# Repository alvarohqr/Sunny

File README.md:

# A LoRaWAN Air Quality and Meteorological monitoring system based on a MSP430FR5529LP Texas Instruments launchpad.

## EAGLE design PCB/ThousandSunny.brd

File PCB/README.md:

Thousand Sunny Printed Circuit Board Files.
Software: EaglePCB for designd and EasyEDA for costumization.

IMPORTANT NOTE: the Protection Circuit uses a IRF9Z34 transistor while the Power Saving Circuit a IRLZ44N.

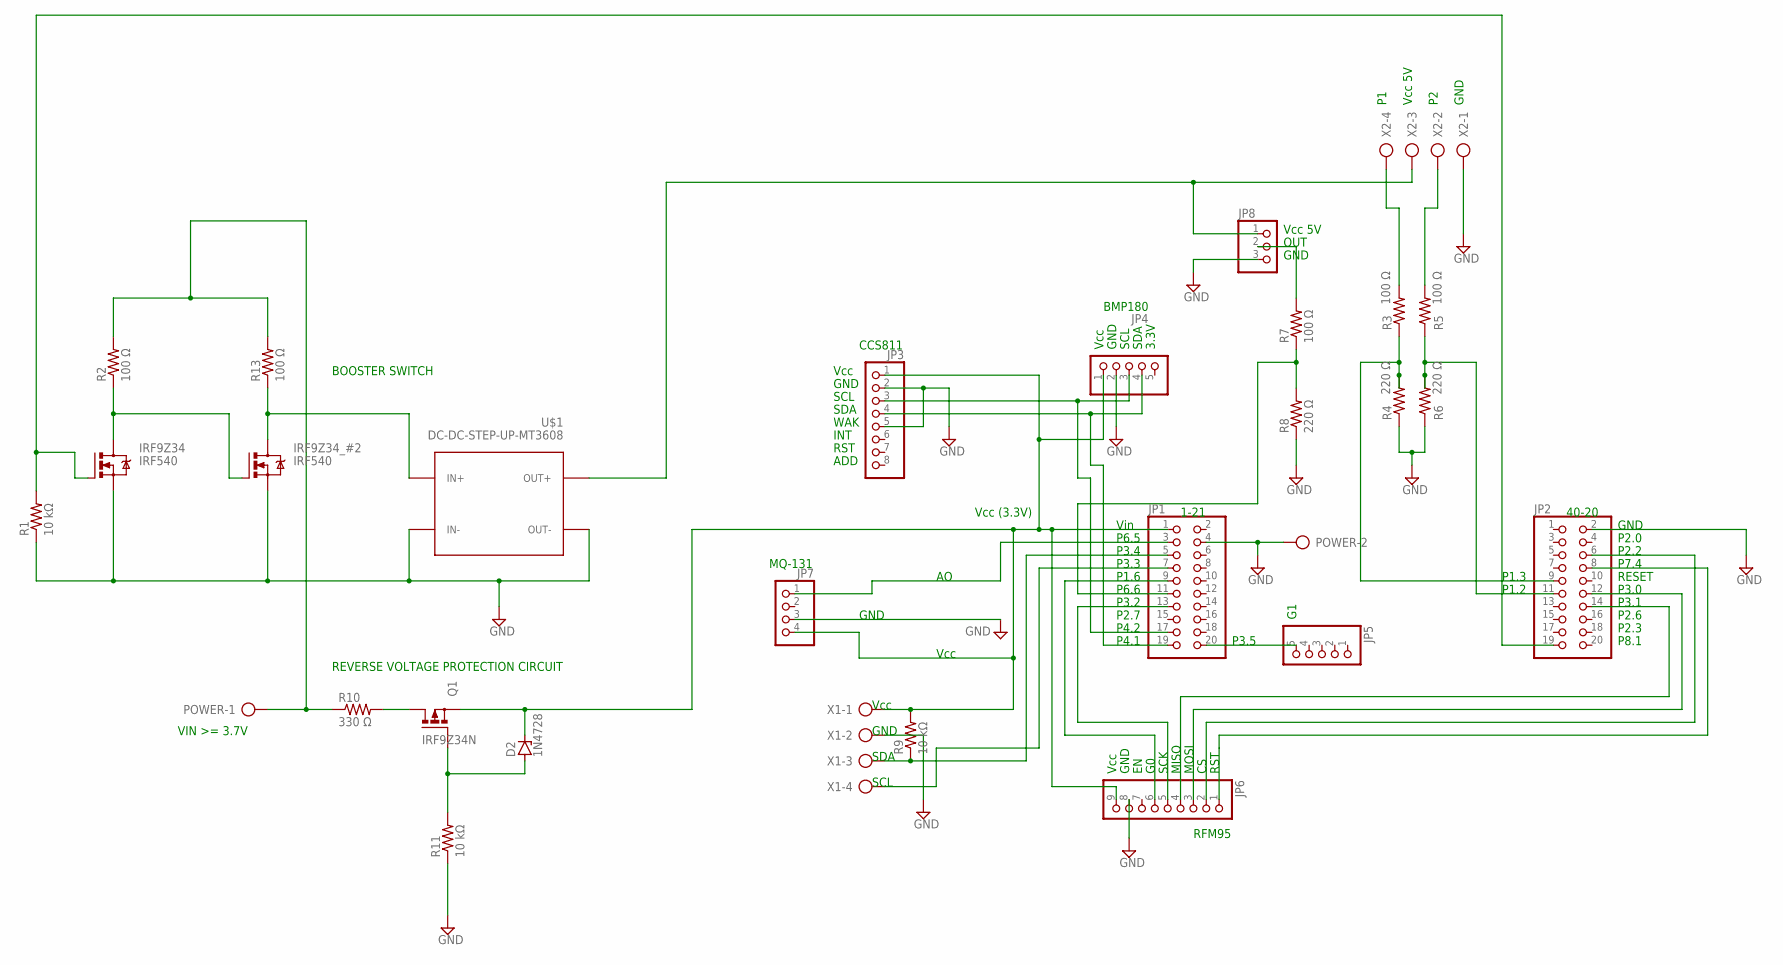
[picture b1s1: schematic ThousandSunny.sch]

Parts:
D2: 1N4728; DO41Z10
IRF9Z34, IRF9Z34_#2: IRF540; TO220BV
JP1, JP2: PINHD-2X10; 2X10
JP3: PINHD-1X8; 1X08
JP4, JP5: PINHD-1X5; 1X05
JP6: PINHD-1X9; 1X09
JP7: PINHD-1X4; 1X04
JP8: PINHD-1X3; 1X03
POWER: AK300/2
Q1: IRF9Z34N; TO220BV
R1, R9, R11: 10 kΩ; 0204/7
R2, R3, R5, R7, R13: 100 Ω; 0204/7
R4, R6, R8: 220 Ω; 0204/7
R10: 330 Ω; 0204/7
U$1: DC-DC-STEP-UP-MT3608
X1, X2: AK300/4

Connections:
ANODE: D2.A, Q1.G, R11.2
BATTERY: POWER.1, R2.2, R10.1, R13.2
D1->G2: IRF9Z34.D, IRF9Z34_#2.G, R2.1
D2->VIN: IRF9Z34_#2.D, R13.1, U$1.IN+
DRAIN_Q1: Q1.D, R10.2
DUST_P1: JP2.9, R3.1, R4.2
DUST_P2: JP2.11, R5.1, R6.2
G1: JP1.20, JP5.5
GND: IRF9Z34.S, IRF9Z34_#2.S, JP1.4, JP2.2, JP3.2, JP3.5, JP4.2, JP6.8, JP7.3, JP8.3, POWER.2, R1.1, R4.1, R6.1, R8.1, R11.1, U$1.IN-, U$1.OUT-, X1.2, X2.1
MISO: JP2.14, JP6.4
MOSI: JP2.12, JP6.3
O3: JP1.3, JP7.1
P8.2: IRF9Z34.G, JP2.19, R1.2
RAW_P1: R3.2, X2.4
RAW_P2: R5.2, X2.2
RAW_SOLAR: JP8.2, R7.2
RFM95W_CS: JP2.6, JP6.2
RFM95W_G0: JP1.9, JP6.6
RFM95_RST: JP2.8, JP6.1
SCK: JP1.13, JP6.5
SCL: JP1.17, JP3.3, JP4.3
SDA: JP1.19, JP3.4, JP4.4
SHT_CLOCK: JP1.7, X1.4
SHT_DATA: JP1.5, R9.1, X1.3
SOLAR: JP1.11, R7.1, R8.2
VIN->DUST: JP8.1, U$1.OUT+, X2.3
VZ->3.3V: D2.C, JP1.1, JP3.1, JP4.1, JP6.9, JP7.4, Q1.S, R9.2, X1.1

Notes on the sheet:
Vcc (3.3V)
Vcc
GND
SCK
MISO
MOSI
RST
Vin
P6.5
P3.4
P3.3
P1.6
P6.6
P3.2
P2.7
P4.2
P4.1
SCL
SDA
WAK
INT
ADD
P2.0
P7.4
RESET
P3.0
P3.1
P2.6
P2.3
P8.1
P2.2
P3.5
P1.3
P1.2
3.3V
Vcc 5V
1-21
40-20
CCS811
BMP180

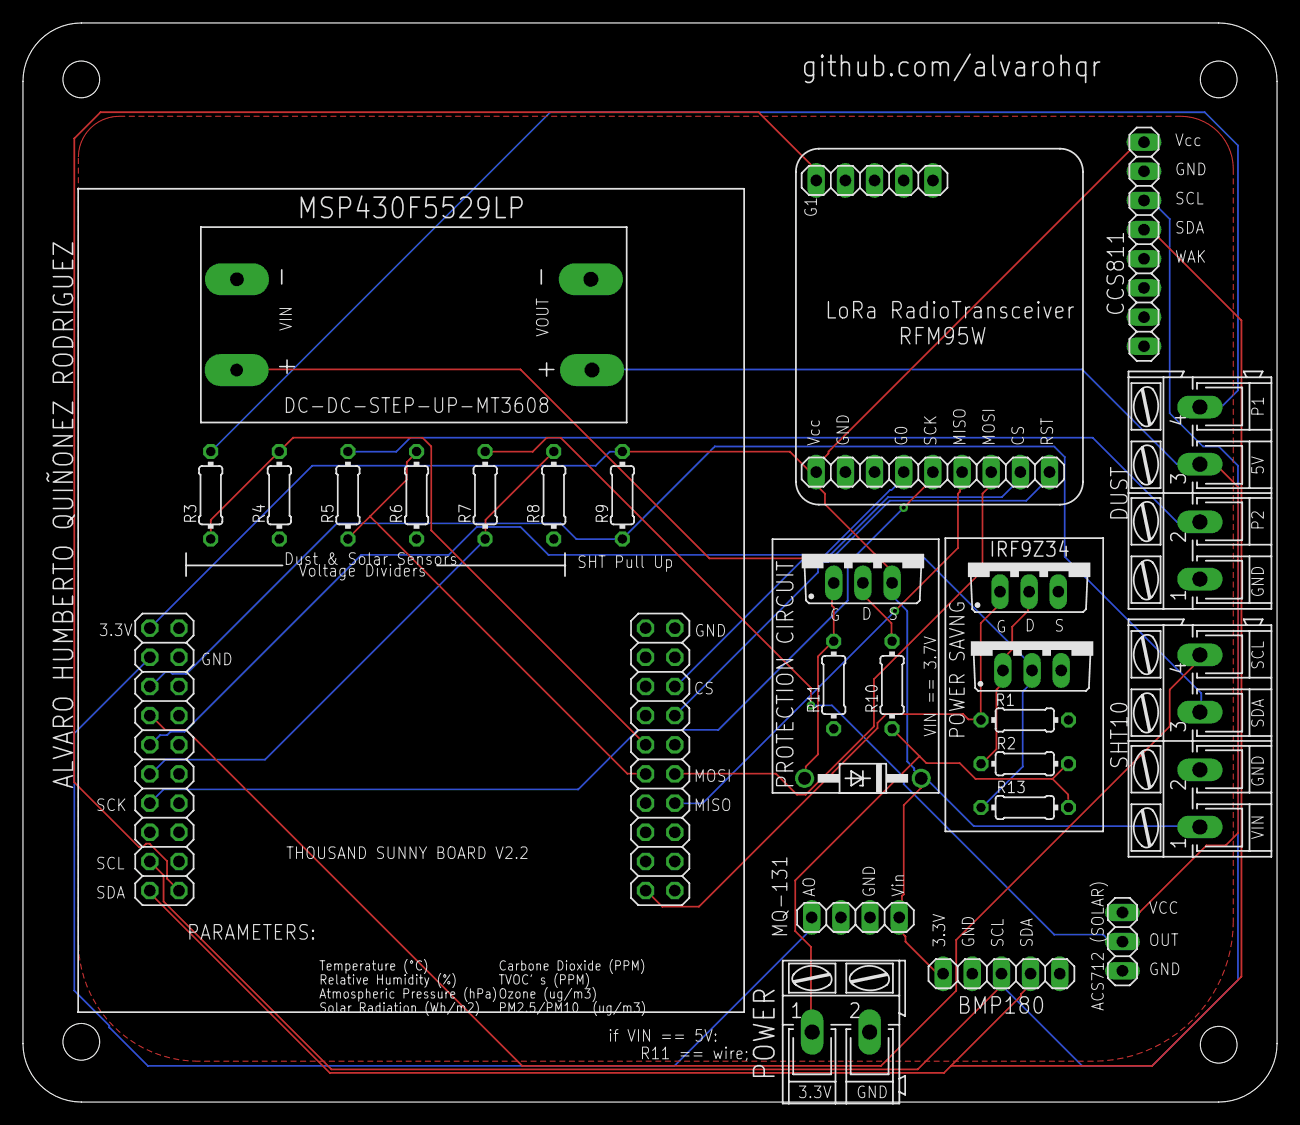
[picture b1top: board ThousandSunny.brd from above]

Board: 2 copper layers, 109.2 x 94.0 mm, 28 parts (1 on the bottom side), 27 nets.

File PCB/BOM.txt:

<<<<<<< HEAD
Part       Value                Device               Package              Description                                  
D2         1N4728               1N4728               DO41Z10              Z DIODE                                      
IRF9Z34    IRF540               IRF540               TO220BV              HEXFET Power MOSFET                          
IRF9Z34_#2 IRF540               IRF540               TO220BV              HEXFET Power MOSFET                          
JP1                             PINHD-2X10           2X10                 PIN HEADER                                   
JP2                             PINHD-2X10           2X10                 PIN HEADER                                   
JP3                             PINHD-1X8            1X08                 PIN HEADER                                   
JP4                             PINHD-1X5            1X05                 PIN HEADER                                   
JP5                             PINHD-1X5            1X05                 PIN HEADER                                   
JP6                             PINHD-1X9            1X09                 PIN HEADER                                   
JP7                             PINHD-1X4            1X04                 PIN HEADER                                   
JP8                             PINHD-1X3            1X03                 PIN HEADER                                   
POWER                           AK300/2              AK300/2              CONNECTOR                                    
Q1         IRF9Z34N             PMOSFET_PTO220BV     TO220BV              Power MOSFET P-Channel                       
R1         10 kΩ                R-US_0204/7          0204/7               RESISTOR, American symbol                    
R2         100 Ω                R-US_0204/7          0204/7               RESISTOR, American symbol                    
R3         100 Ω                R-US_0204/7          0204/7               RESISTOR, American symbol                    
R4         220 Ω                R-US_0204/7          0204/7               RESISTOR, American symbol                    
R5         100 Ω                R-US_0204/7          0204/7               RESISTOR, American symbol                    
R6         220 Ω                R-US_0204/7          0204/7               RESISTOR, American symbol                    
R7         100 Ω                R-US_0204/7          0204/7               RESISTOR, American symbol                    
R8         220 Ω                R-US_0204/7          0204/7               RESISTOR, American symbol                    
R9         10 kΩ                R-US_0204/7          0204/7               RESISTOR, American symbol                    
R10        330 Ω                R-US_0204/7          0204/7               RESISTOR, American symbol                    
R11        10 kΩ                R-US_0204/7          0204/7               RESISTOR, American symbol                    
R13        100 Ω                R-US_0204/7          0204/7               RESISTOR, American symbol                    
U$1        DC-DC-STEP-UP-MT3608 DC-DC-STEP-UP-MT3608 DC-DC-STEP-UP-MT3608 DC/DC Step-Up Regulator based on MT3608 chip 
X1                              AK300/4              AK300/4              CONNECTOR                                    
X2                              AK300/4              AK300/4              CONNECTOR                                    
=======
Qty Value                Device               Package              Parts               Description                                  MF MPN OC_FARNELL OC_NEWARK POPULARITY
1                        AK300/2              AK300/2              POWER               CONNECTOR                                           unknown    unknown   16        
2                        AK300/4              AK300/4              X1, X2              CONNECTOR                                           unknown    unknown   0         
1                        PINHD-1X3            1X03                 JP8                 PIN HEADER                                                               92        
1                        PINHD-1X4            1X04                 JP7                 PIN HEADER                                                               91        
2                        PINHD-1X5            1X05                 JP4, JP5            PIN HEADER                                                               69        
1                        PINHD-1X8            1X08                 JP3                 PIN HEADER                                                               67        
1                        PINHD-1X9            1X09                 JP6                 PIN HEADER                                                               13        
2                        PINHD-2X10           2X10                 JP1, JP2            PIN HEADER                                                               7         
3   10 kΩ                R-US_0204/7          0204/7               R1, R9, R11         RESISTOR, American symbol                                                          
5   100 Ω                R-US_0204/7          0204/7               R2, R3, R5, R7, R13 RESISTOR, American symbol                                                          
1   1N4728               1N4728               DO41Z10              D2                  Z DIODE                                                                  6         
3   220 Ω                R-US_0204/7          0204/7               R4, R6, R8          RESISTOR, American symbol                                                          
1   330 Ω                R-US_0204/7          0204/7               R10                 RESISTOR, American symbol                                                          
1   DC-DC-STEP-UP-MT3608 DC-DC-STEP-UP-MT3608 DC-DC-STEP-UP-MT3608 U$1                 DC/DC Step-Up Regulator based on MT3608 chip                                       
2   IRF540               IRF540               TO220BV              IRF9Z34, IRF9Z34_#2 HEXFET Power MOSFET                                                      7         
1   IRF9Z34N             PMOSFET_PTO220BV     TO220BV              Q1                  Power MOSFET P-Channel                                                   2         
>>>>>>> 71eeb520dceeb38ec552c8eefd7f92005e78dd0f

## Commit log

2022-09-26 Thousand Sunny V1
2022-10-05 Added project description
2022-10-05 Project description
2022-10-05 Main code
2022-10-05 Main project
2022-10-05 The Things Network module
2022-10-05 TTN settings
2022-10-05 Pin Map
2022-10-05 Summary
2022-10-05 Sensor node components summary
2022-10-05 Sensor node summary
2022-10-05 End Node
2022-10-05 Source Files
2022-10-05 Interact Adafruit devices
2022-10-05 Components Source Files
2022-10-05 Sensor Node
2022-10-06 Decoder
2022-10-06 Retrieving data via the TTN's MQTT topic
2022-10-06 Gateway files
2022-10-09 Board logo
2022-10-09 Schematic
2022-10-09 PDF file
2022-10-09 CAM config
2022-10-09 Gerber files
2022-10-09 PCB files
2022-10-16 Components
2022-10-18 Power Consumption Data
2022-12-30 Board Bill of Materials
2022-12-30 Update BOM.txt
    Board Bill of Materials
2022-12-30 CAM Files
2022-12-30 Print Files
2022-12-30 Updated Files
2022-12-30 ThousandSunny PCB
2023-01-20 Gateway Firmware
